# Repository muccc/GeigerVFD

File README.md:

# Geiger counter with Vacuum fluorescent display
This repo is a collection of all the parts to build an [ESP32](https://www.espressif.com/en/products/socs/esp32) based handheld device to measure radioactivity with a [Geiger–Müller tube](https://en.wikipedia.org/wiki/Geiger%E2%80%93M%C3%BCller_tube) & display info on an [VFD](https://en.wikipedia.org/wiki/Vacuum_fluorescent_display).

Future plans are [Home Automation](https://esphome.io/) integration, logging radioactivity measurements over WiFi & displaying additional information like e.g. a Clock.

The device is be powered via Micro-USB port of the ESP32. Note that the current draw of the VFD may exceed the 500mA USB standard.

# PCB
The PCB is designed in [KiCad](https://www.kicad.org/). All source files are in the  [pcb](pcb) Subdirectory.

### Schematic:

### PCB:

### 3d render view:

# Case
The Case is designed in [OpenSCAD](https://openscad.org/). Sources reside in the [case](case/) Subdirectory.

# Firmware
:warning: Work in Progress :warning:

The firmware is written using [Espressif-IDF](https://docs.espressif.com/projects/esp-idf/en/latest/esp32/get-started/) and lives in the [firmware](firmware/) directory.

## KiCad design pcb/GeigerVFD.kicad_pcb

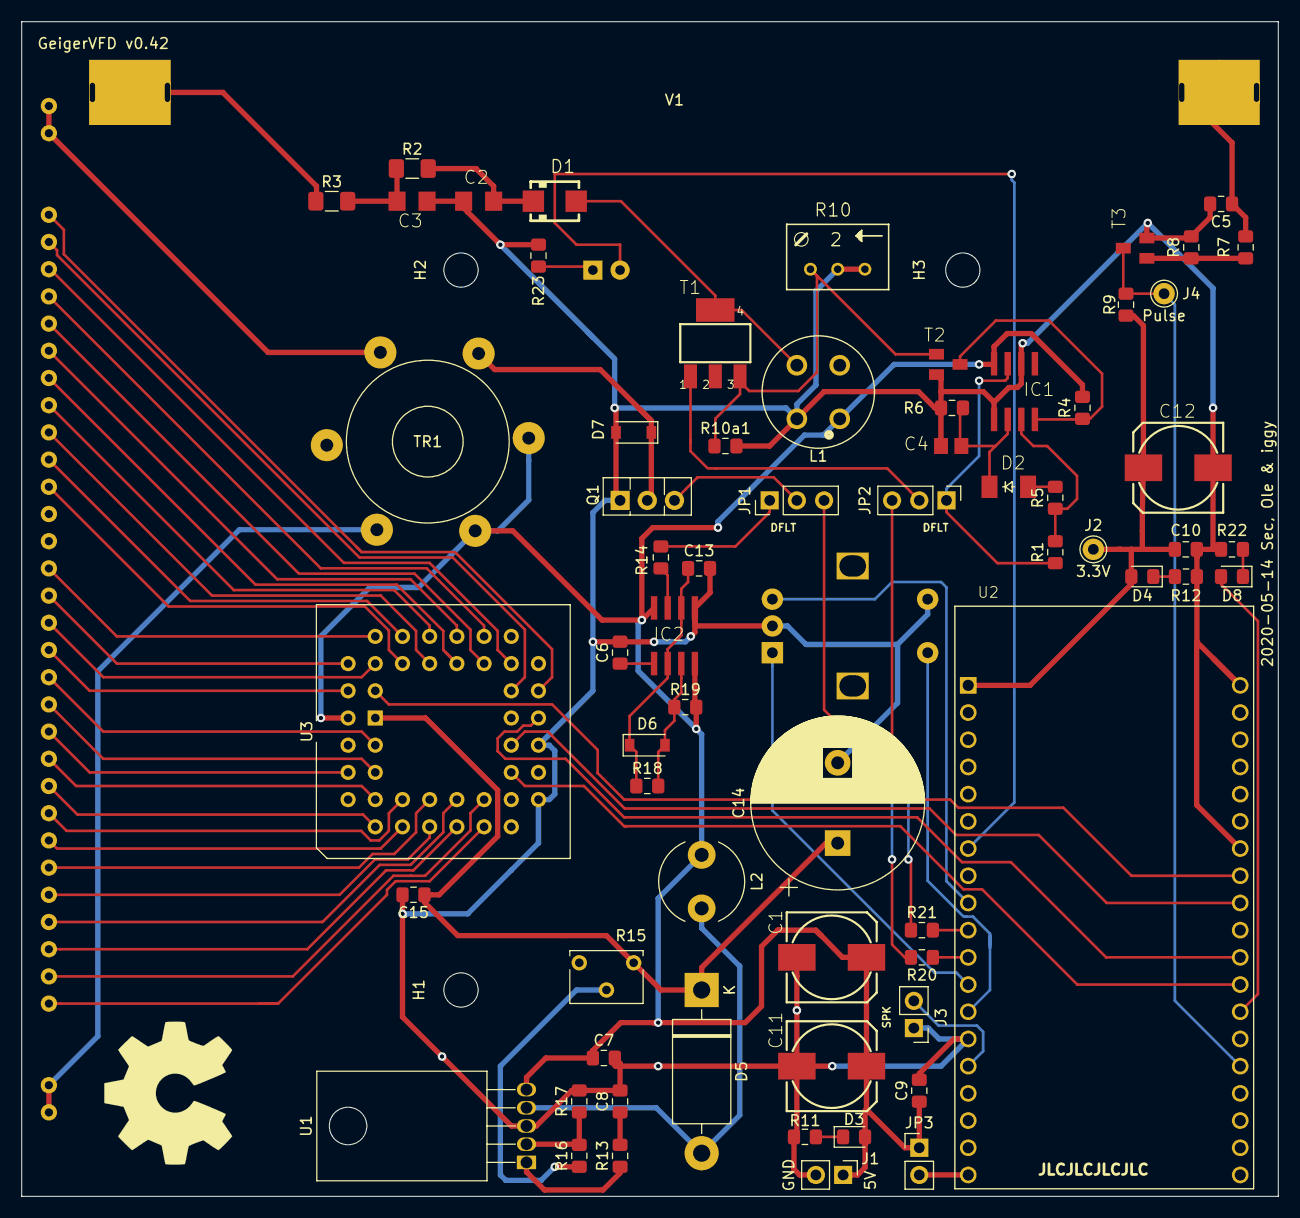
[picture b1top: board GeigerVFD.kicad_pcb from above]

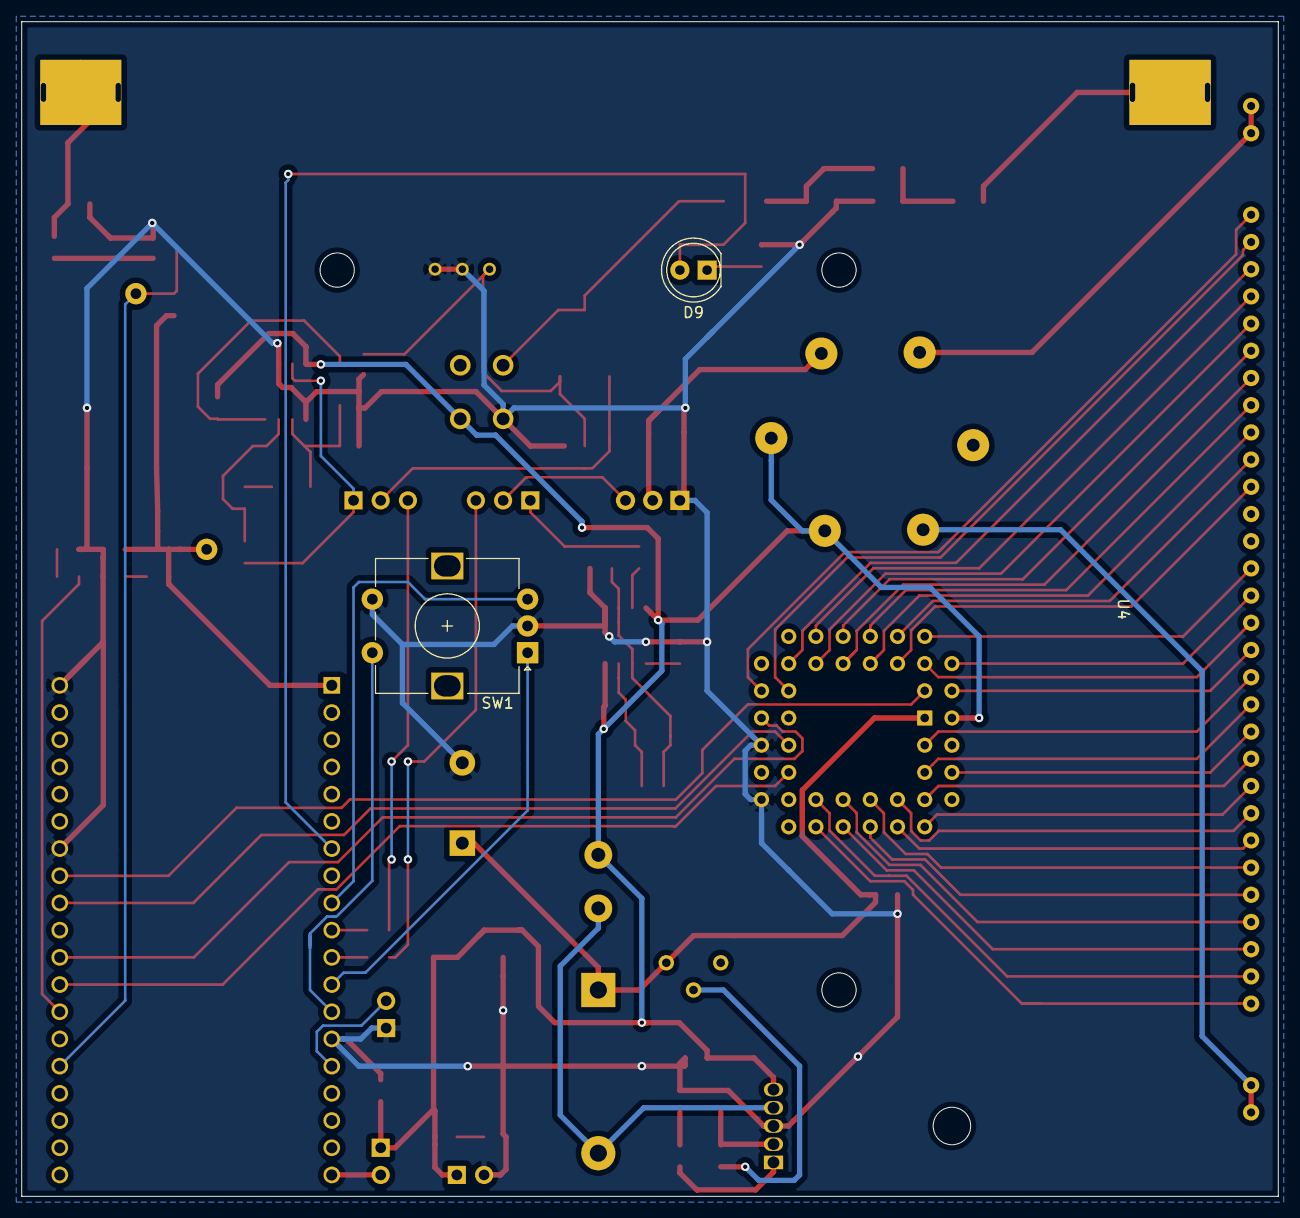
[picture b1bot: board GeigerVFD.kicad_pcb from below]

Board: 2 copper layers, 117.3 x 109.7 mm, 74 parts (3 on the bottom side), 79 nets.

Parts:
C1: 220uF; 153CLV-0810
C2, C3: 10nF/1k; C1206
C4: 1nF; C0805
C5: 330p; C_0805_2012Metric_Pad1.15x1.40mm_HandSolder
C6: 10n; C_0805_2012Metric_Pad1.15x1.40mm_HandSolder
C7, C9, C10, C15: 100n; C_0805_2012Metric_Pad1.15x1.40mm_HandSolder
C8: 330n; C_0805_2012Metric_Pad1.15x1.40mm_HandSolder
C11, C12: 10uF; 153CLV-0810
C13: 4.7n; C_0805_2012Metric_Pad1.15x1.40mm_HandSolder
C14: 1000µ; CP_Radial_D16.0mm_P7.50mm
D1: BYG23M; SMA
D2: 1N4148; SOD-123_MINI-SMA
D3: green; LED_0805_2012Metric_Pad1.15x1.40mm_HandSolder
D4: yellow; LED_0805_2012Metric_Pad1.15x1.40mm_HandSolder
D5: 1N5822; D_DO-201AD_P15.24mm_Horizontal
D6, D7: 1N4148; D_SOD-123
D8: red; LED_0805_2012Metric_Pad1.15x1.40mm_HandSolder
D9: red; LED_D5.0mm
H1, H2, H3: MountingHole; MountingHole_3.2mm_M3_DIN965
IC1: TLC555; SO08
IC2: LM555; SO08
J1, J3: Conn_01x02_Male; PinHeader_1x02_P2.54mm_Vertical
J2: 3.3V; Pin_D1.0mm_L10.0mm
J4: Pulse; Pin_D1.0mm_L10.0mm
JP1, JP2: Jumper3; PinHeader_1x03_P2.54mm_Vertical
JP3: Jumper; PinHeader_1x02_P2.54mm_Vertical
L1: 15mH; 1200LRS
L2: 100µ; L_Radial_D7.8mm_P5.00mm_Fastron_07HCP
LOGO1: Logo_Open_Hardware_Large; OSHW-Symbol_13.4x12mm_SilkScreen
Q1: BD137; TO-126-3_Vertical
R1, R11, R12, R14, R16, R18, R19, R22, R23: 1k; R_0805_2012Metric_Pad1.15x1.40mm_HandSolder
R2: 1M; R_1206_3216Metric_Pad1.42x1.75mm_HandSolder
R3: 4.7M; R_1206_3216Metric_Pad1.42x1.75mm_HandSolder
R4, R8: 100k; R_0805_2012Metric_Pad1.15x1.40mm_HandSolder
R5: 330; R_0805_2012Metric_Pad1.15x1.40mm_HandSolder
R6: 220k; R_0805_2012Metric_Pad1.15x1.40mm_HandSolder
R7: 1.5k; R_0805_2012Metric_Pad1.15x1.40mm_HandSolder
R9: 27k; R_0805_2012Metric_Pad1.15x1.40mm_HandSolder
R10: 100; RJ9W
R10a1: 30R; R_0805_2012Metric_Pad1.15x1.40mm_HandSolder
R13, R17: 2.2k; R_0805_2012Metric_Pad1.15x1.40mm_HandSolder
R15: 100k; Potentiometer_Vishay_T73XX_Horizontal
R20, R21: 680; R_0805_2012Metric_Pad1.15x1.40mm_HandSolder
SW1: Rotary_Encoder_Switch; RotaryEncoder_Alps_EC12E-Switch_Vertical_H20mm
T1: STN0214; SOT223
T2, T3: 2N4401; SOT23
TR1: Transformer_1P_SS; Transformer_Toroid_Tapped_Horizontal_D14.0mm_Amidon-T50
U1: LM2577; TO-220-5_Horizontal_TabDown
U2: ESP32-DEVKITC-32D; MODULE_ESP32-DEVKITC-32D
U3: MAX6934; PLCC-44_THT-Socket
U4: FV651G
V1: GM-Tube; Tube

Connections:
+3V3: C10.1, C12.+, D4.2, J2.1, R9.2, U2.1
+5V: C1.+, C7.1, C9.1, C11.+, D3.2, IC1.8, IC2.4, IC2.8, J1.1, JP3.1, L1.P1, L2.1, R4.2, R19.2, TR1.1, TR1.4, U1.5, U3.44
/01G: U3.38, U4.24
/02G: U3.37, U4.25
/03G: U3.36, U4.26
/04G: U3.35, U4.27
/05G: U3.34, U4.28
/06G: U3.33, U4.29
/07G: U3.32, U4.30
/08G: U3.31, U4.31
/09G: U3.30, U4.32
/10G: U3.27, U4.33
/11G: U3.26, U4.34
/HV+: R3.1, V1.1
/HV-: C5.1, R7.1, V1.2
/P01: U3.39, U4.21
/P02: U3.40, U4.20
/P03: U3.41, U4.19
/P04: U3.42, U4.18
/P05: U3.3, U4.17
/P06: U3.5, U4.16
/P07: U3.4, U4.15
/P08: U3.8, U4.14
/P09: U3.7, U4.13
/P10: U3.10, U4.12
/P11: U3.9, U4.11
/P12: U3.12, U4.10
/P13: U3.11, U4.9
/P14: U3.14, U4.8
/P15: U3.13, U4.7
/P16: U3.16, U4.6
/P17: U3.15, U4.5
Fil1: TR1.5, U4.1, U4.2
Fil2: TR1.3, U4.37, U4.38
GND: C1.-, C2.2, C3.2, C4.1, C5.2, C6.2, C7.2, C8.2, C9.2, C10.2, C11.-, C12.-, C13.2, C14.2, C15.2, D7.2, IC1.1, IC1.6, IC2.1, J1.2, J3.1, L1.P4, Q1.1, R6.2, R8.2, R10.E, R10.S, R10a1.2, R11.2, R12.2, R17.2, R22.2, R23.2, SW1.C, SW1.S2, T2.2, T3.2, U1.3, U2.14, U2.20, U2.26, U3.18, U3.22
unnamed: C2.1, D1.C, R2.2
unnamed: C3.1, R2.1, R3.2
unnamed: C4.2, D2.C, IC1.2, R6.1
unnamed: C6.1, IC2.5
unnamed: C8.1, R13.2
unnamed: C13.1, D6.1, IC2.2, IC2.6, R18.1
unnamed: D1.A, L1.P3, T1.4
unnamed: D2.A, R5.2
unnamed: D3.1, R11.1
unnamed: D4.1, R12.1
unnamed: D5.2, L2.2, U1.4
unnamed: D6.2, IC2.7, R18.2, R19.1
unnamed: D7.1, Q1.2, TR1.2
unnamed: D8.1, R22.1
unnamed: D8.2, U2.32
unnamed: D9.1, R23.1
unnamed: D9.2, U2.7
unnamed: IC1.3, R1.2, R5.1
unnamed: IC1.7, JP2.1, R1.1
unnamed: IC2.3, R14.2
unnamed: J3.2, U2.15
unnamed: J4.1, R9.1, T3.3, U2.34
unnamed: JP1.1, R14.1
unnamed: JP1.2, Q1.3
unnamed: JP1.3, R20.2
unnamed: JP2.2, T1.1
unnamed: JP2.3, R21.1
unnamed: JP3.2, U2.19
unnamed: R7.2, R8.1, T3.1
unnamed: R10.A, R10a1.1, T1.3, T2.1
unnamed: R13.1, U1.1
unnamed: R15.2, R16.1
unnamed: R16.2, R17.1, U1.2
unnamed: R20.1, U2.11
unnamed: R21.2, U2.10
unnamed: SW1.A, U2.12
unnamed: SW1.B, U2.9
unnamed: SW1.S1, U2.13
unnamed: U2.27, U3.43
unnamed: U2.28, U3.23
unnamed: U2.30, U3.24
unnamed: U2.31, U3.21
R: IC1.4, R4.1, T2.3
Vdd: C14.1, C15.1, D5.1, R15.1, U3.1

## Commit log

2020-03-21 Created MAX6934 and VFD symbols
2020-03-21 Add DATASHEETS.txt
2020-03-21 Make pin text smaller
2020-03-21 ignore more cache
2020-03-25 Add LM2577
2020-03-25 Add Voltage generation
2020-03-25 add some documentation
2020-04-06 connect vfd & add footprint
2020-04-29 Include Geiger circuit & replace ESP
2020-04-30 Update footprints
2020-05-05 Update footprints & fix bugs
2020-05-05 First sort of PCB
2020-05-07 Add GM-Tube. First pass at PCB
2020-05-07 Fix annotations of PiGi subsection. Fix some footprint issues. More PCB routing Add Geiger Tube
2020-05-07 Fix GM Tube Footprint Add Power flags for ERC Fix VFD symbol to use pin stacking
2020-05-09 Shrink & route & add rotary encoder & add 3d models
2020-05-10 Convert Eagle R to Kicad Add Buzzer header & Warn LED
2020-05-13 Finish PCB
2020-05-13 openscad files for case - initial commit
2020-05-14 finalize
2020-12-28 change case dimensions according to reality
2020-12-28 Case: Replaced reference image with readme.txt
2020-12-28 README.txt.txt -> README.txt
2020-12-28 fix in knob.scad
2020-12-28 added .stl for all parts
2021-01-12 increaded case bode height and moved usb cutout position
2021-04-07 fix MAX6934 connections: Vcc to 3.3V instead of 5V & DIN to MOSI instead of MISO
2021-12-28 Move pcb things to own subdir
2021-12-28 add first demo firmware
2022-01-05 Add readme & some images
